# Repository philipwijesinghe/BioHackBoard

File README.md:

# BioHackBoard

The BioHackBaord is an Arduino shield that aims to eliminate the need for any soldering or breadboard for the assembly of BHA devices. 

The shield is able to drive a steppermotor, read a rotary encoders, 2 thermistors, control 2 MOSFETs and connect up to 3 I2C devices, such as an LCD screen.

## Releases

The current version (v2.1) of the board has been designed on the Circuits.io platform. The schematics, PCB design and Gerber files can be found in that [BioHackBoard V2.1 repo](https://circuits.io/circuits/2997842-biohack-board)

The BoM file in this repo lists the parts needed to finish this v2.1 board.

The first version of the board and a kit with additional components was sold by [BioTronics](http://biotronics.nl/products/biohackacademy-prototyping-kit). The source files of this board can be found in this BioHackBoard repository.

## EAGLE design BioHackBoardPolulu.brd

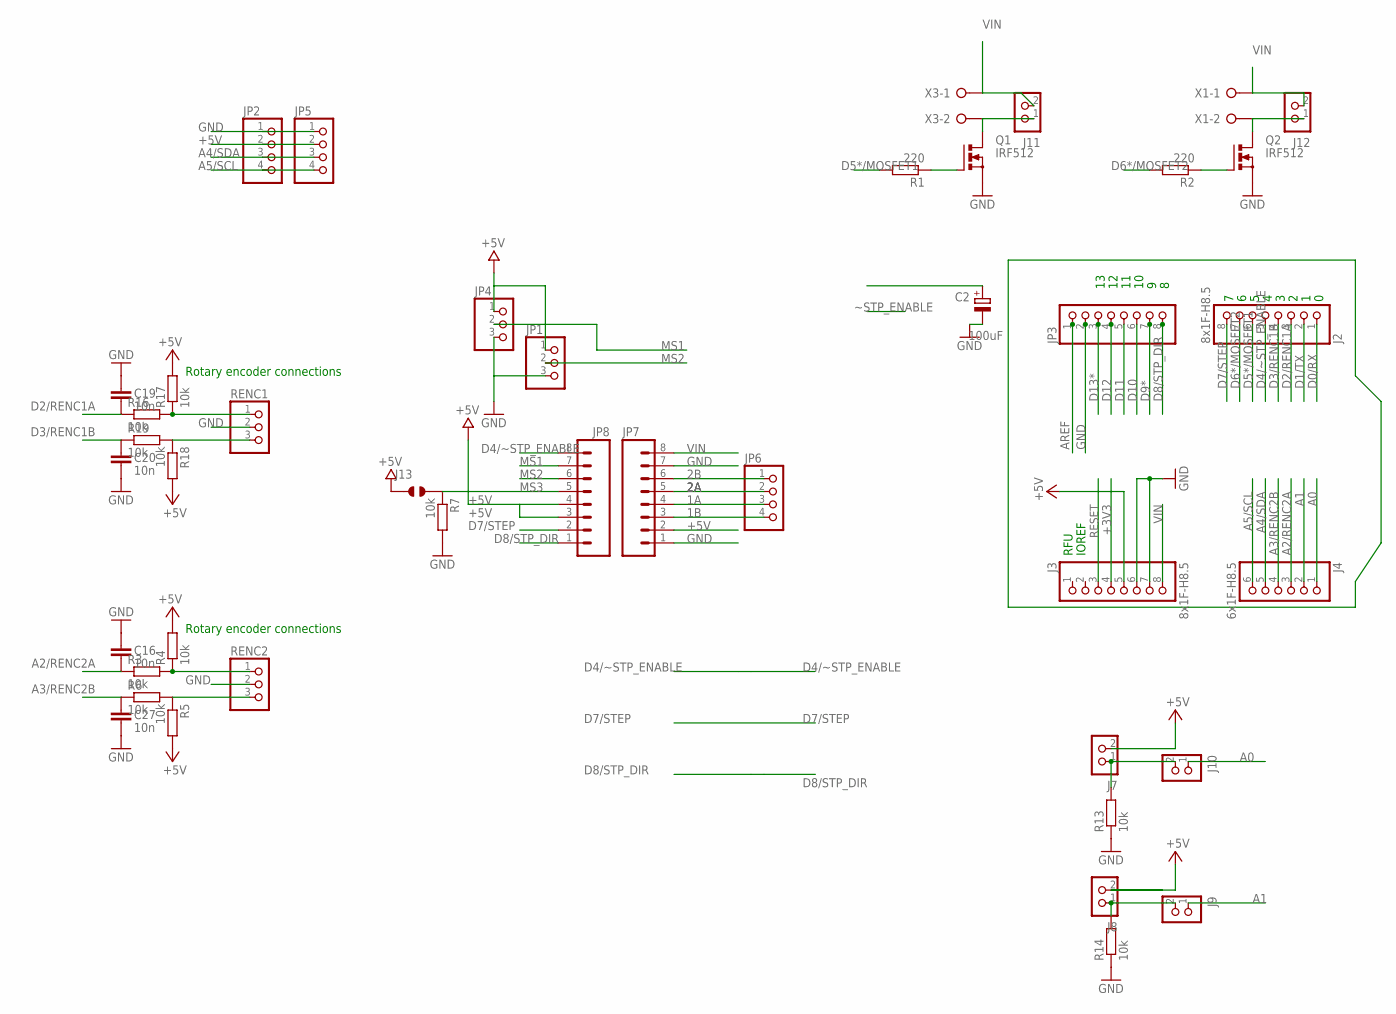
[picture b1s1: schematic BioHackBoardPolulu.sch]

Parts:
C2: 100uF; E2,5-7
C16, C19, C20, C27: 10n; C0603-ROUND
J2, J3: 8x1F-H8.5; 1X08-S
J4: 6x1F-H8.5; 1X06-S
J7, J8, J9, J10, J11, J12: CON_HEADER_1X02-PTH; M1X2
J13: JUMPER_SOLDER_1X2
JP1, JP4: PINHD-1X03_2.54-S; 1X03-S
JP2, JP5, JP6: PINHD-1X04_2.54-S; 1X04-S
JP3: PINHD-1X08_2.54-S; 1X08-S
JP7, JP8: M081X08; 1X08
Q1, Q2: IRF512; TO220BV
R1, R2: 220; R0603-ROUND
R3, R4, R5, R6, R7, R16, R17, R18, R19: 10k; R0603-ROUND
R13, R14: 10k; R0603
RENC1, RENC2: PINHD-1X03_2.54-S; 1X03-S
X1, X3: W237-02P; W237-132

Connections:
1A: JP6.3, JP7.4
1B: JP6.4, JP7.3
2A: JP6.2, JP7.5
2B: JP6.1, JP7.6
+3V3: J3.4
+5V: J3.5, J7.2, J8.2, J13.1, JP1.1, JP2.2, JP4.1, JP5.2, JP7.2, JP8.3, JP8.4, R4.2, R5.2, R17.2, R18.2
A0: J4.1, J10.1
A0P: J7.1, J10.2, R13.2
A1: J4.2, J9.1
A1P: J8.1, J9.2, R14.2
A2/RENC2A: C16.1, J4.3, R3.1
A3/RENC2B: C27.2, J4.4, R6.1
A4/SDA: J4.5, JP2.3, JP5.3
A5/SCL: J4.6, JP2.4, JP5.4
AREF: JP3.1
D0/RX: J2.1
D1/TX: J2.2
D2/RENC1A: C19.1, J2.3, R16.1
D3/RENC1B: C20.2, J2.4, R19.1
D4/~STP_ENABLE: J2.5, JP8.8
D5*/MOSFET1: J2.6, R1.2
D6*/MOSFET2: J2.7, R2.2
D7/STEP: J2.8, JP8.2
D8/STP_DIR: JP3.8, JP8.1
D9*: JP3.7
D10: JP3.6
D11: JP3.5
D12: JP3.4
D13*: JP3.3
GND: C2.-, C16.2, C19.2, C20.1, C27.1, J3.6, J3.7, JP1.3, JP2.1, JP3.2, JP4.3, JP5.1, JP7.1, JP7.7, Q1.S, Q2.S, R7.2, R13.1, R14.1, RENC1.2, RENC2.2
MS1: JP4.2, JP8.7
MS2: JP1.2, JP8.6
MS3: J13.2, JP8.5, R7.1
unnamed: R16.2, R17.1, RENC1.1
unnamed: R3.2, R4.1, RENC2.1
unnamed: Q2.G, R2.1
unnamed: R18.1, R19.2, RENC1.3
unnamed: Q1.G, R1.1
unnamed: R5.1, R6.2, RENC2.3
unnamed: J11.1, Q1.D, X3.2
unnamed: J12.1, Q2.D, X1.2
RESET: J3.3
VIN: C2.+, J3.8, J11.2, J12.2, JP7.8, X1.1, X3.1

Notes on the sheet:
IOREF
RFU
Rotary encoder connections

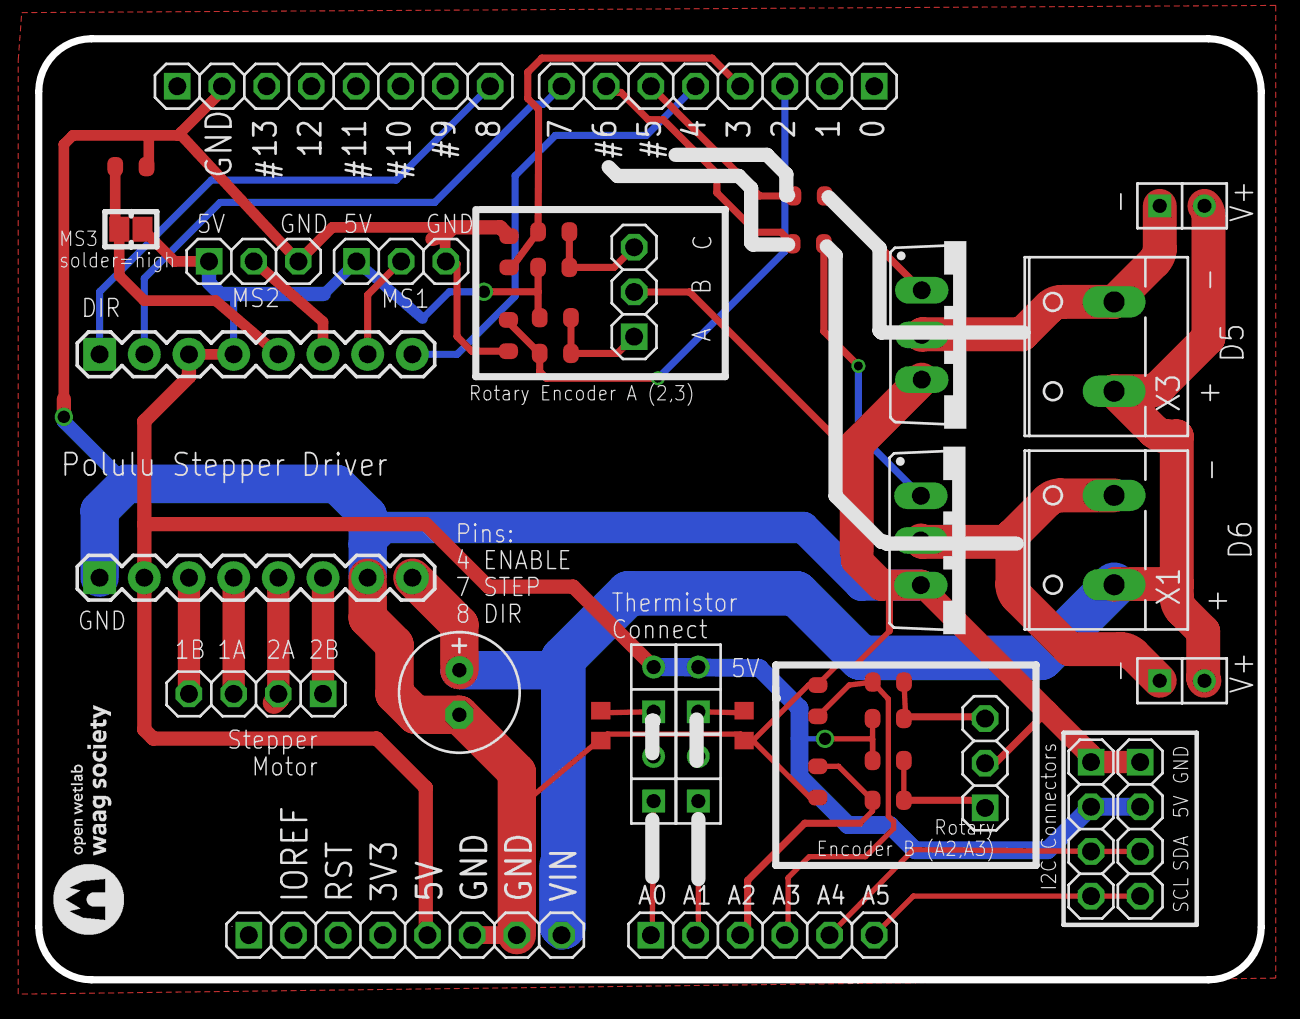
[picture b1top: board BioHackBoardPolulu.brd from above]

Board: 2 copper layers, 69.5 x 53.5 mm, 42 parts (0 on the bottom side), 33 nets.

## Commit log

2015-07-30 * BioHackBoard source files
2015-07-30 * Arduino test/example code
2015-07-30 * Documentation slide
2015-08-01 * A4982 stepper driver board. Work in progress (It uses reference design from the datasheet but so far only tested with faulty clone ICs)
2016-02-10 pin update
2016-02-15 BioHackBoard Fritzing file
2016-03-07 * Biohackboard version that's shipped.
2016-07-31 reorganizing files
2016-11-25 assembly pictures
2016-12-16 BHA4 update
2017-01-04 Example stepper motor control for BioHack Board
    Added an example for stepper motor control using AccelStepper library.
    It includes acceleration and absolute position tracking.

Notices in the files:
parts and their libraries:
SparkFun-Connectors: Licensing: CC v3.0 Share-Alike You are welcome to use this library for commercial purposes.
